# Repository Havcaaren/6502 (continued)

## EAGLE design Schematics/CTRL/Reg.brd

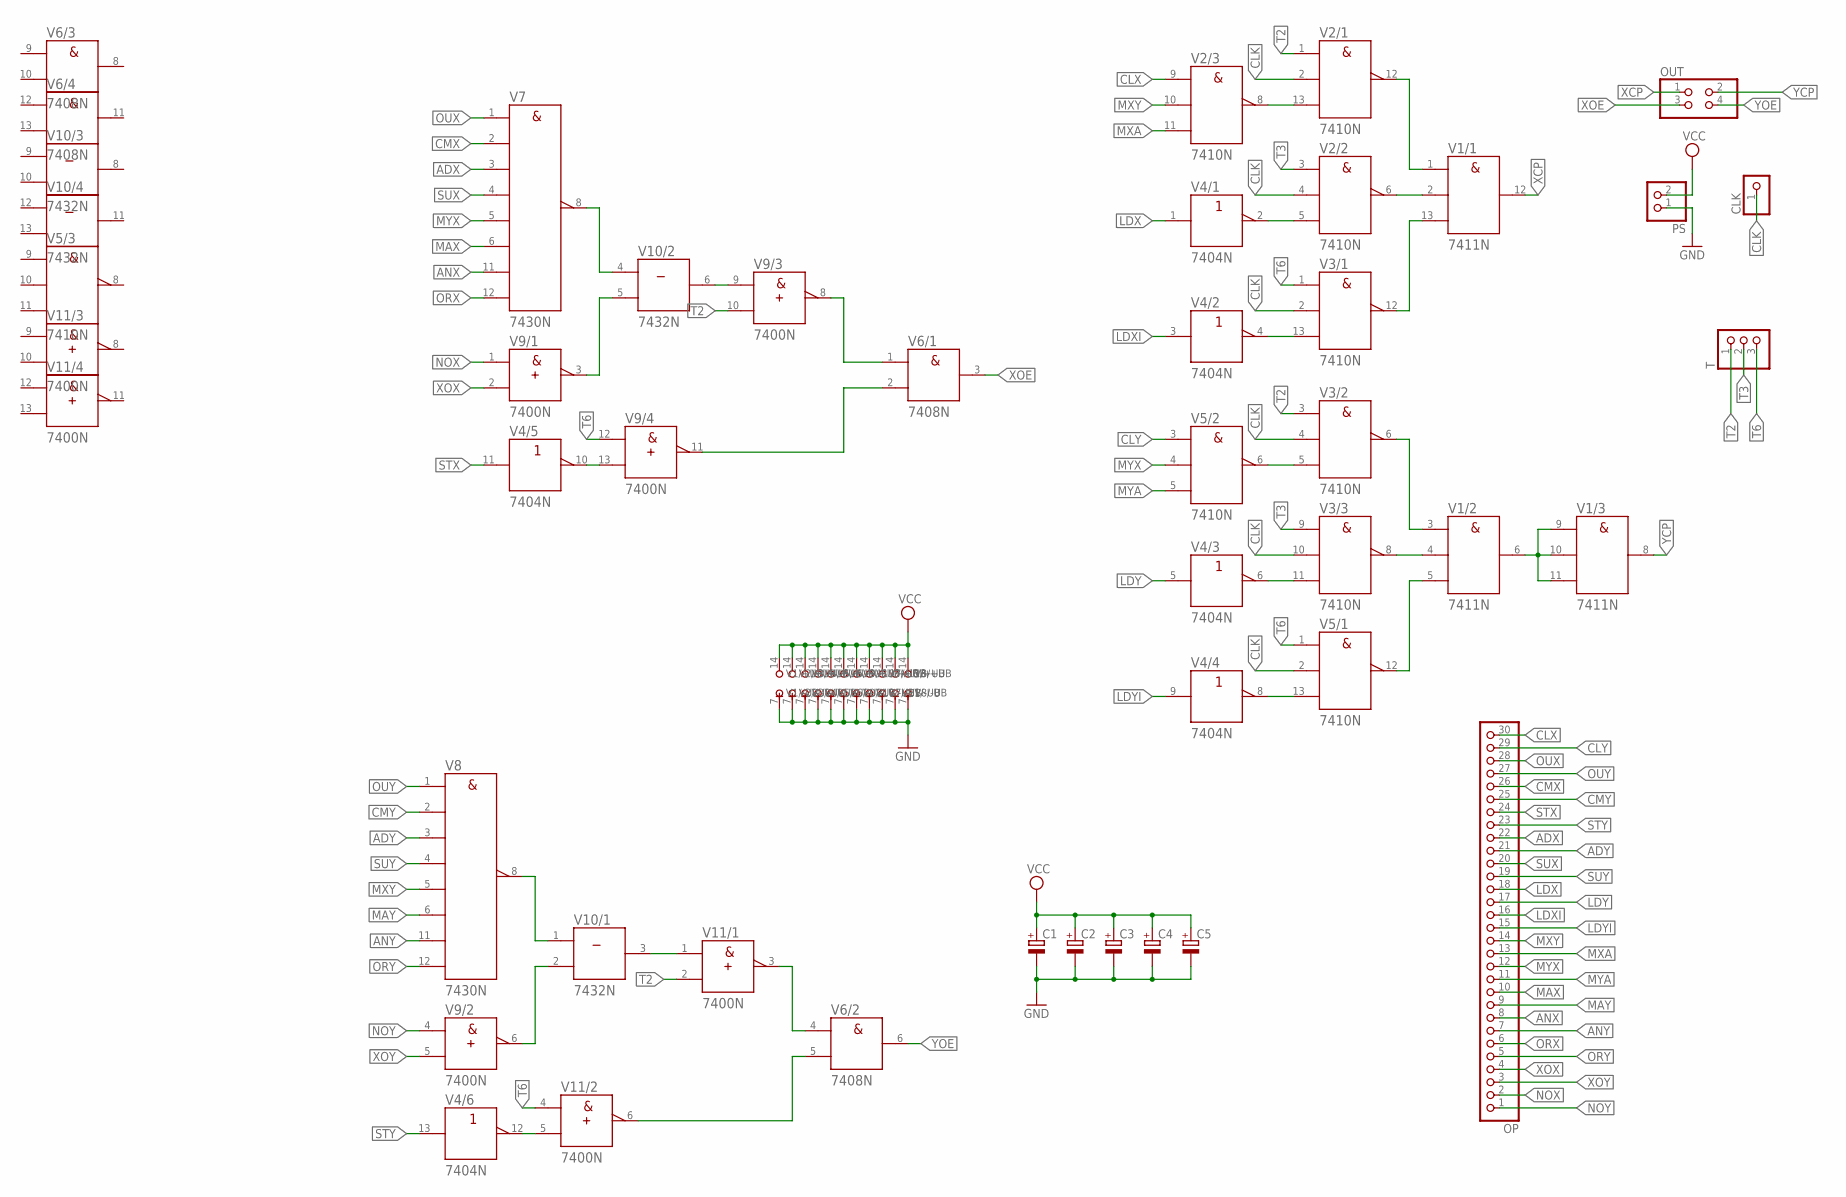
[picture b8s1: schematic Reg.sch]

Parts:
C1, C2, C3, C4, C5: CPOL-EUE2-5; E2-5
CLK: PINHD-1X1; 1X01
OP: PINHD-1X30; 1X30
OUT: PINHD-2X2; 2X02
PS: PINHD-1X2; 1X02
T: PINHD-1X3; 1X03
V1: 7411N; DIL14
V2, V3, V5: 7410N; DIL14
V4: 7404N; DIL14
V6: 7408N; DIL14
V7, V8: 7430N; DIL14
V9, V11: 7400N; DIL14
V10: 7432N; DIL14

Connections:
ADX: OP.22, V7.3 (C)
ADY: OP.21, V8.3 (C)
ANX: OP.8, V7.11 (G)
ANY: OP.7, V8.11 (G)
CLK: CLK.1, V2.2 (B), V2.4 (B), V3.2 (B), V3.4 (B), V3.10 (B), V5.2 (B)
CLX: OP.30, V2.9 (A)
CLY: OP.29, V5.3 (A)
CMX: OP.26, V7.2 (B)
CMY: OP.25, V8.2 (B)
GND: C1.-, C2.-, C3.-, C4.-, C5.-, PS.1, V1.7 (-UB), V2.7 (-UB), V3.7 (-UB), V4.7 (-UB), V5.7 (-UB), V6.7 (-UB), V7.7 (-UB), V8.7 (-UB), V9.7 (-UB), V10.7 (-UB), V11.7 (-UB)
LDX: OP.18, V4.1 (A)
LDXI: OP.16, V4.3 (A)
LDY: OP.17, V4.5 (A)
LDYI: OP.15, V4.9 (A)
MAX: OP.10, V7.6 (F)
MAY: OP.9, V8.6 (F)
MXA: OP.13, V2.11 (C)
MXY: OP.14, V2.10 (B), V8.5 (E)
MYA: OP.11, V5.5 (C)
MYX: OP.12, V5.4 (B), V7.5 (E)
unnamed: V1.3 (A), V3.6 (Y)
unnamed: V1.2 (B), V2.6 (Y)
unnamed: V1.1 (A), V2.12 (Y)
unnamed: V1.13 (C), V3.12 (Y)
unnamed: V1.6 (Y), V1.9 (A), V1.10 (B), V1.11 (C)
unnamed: V1.4 (B), V3.8 (Y)
unnamed: V1.5 (C), V5.12 (Y)
unnamed: V9.9 (A), V10.6 (Y)
unnamed: V4.10 (Y), V9.13 (B)
unnamed: V2.8 (Y), V2.13 (C)
unnamed: V6.1 (A), V9.8 (Y)
unnamed: V6.2 (B), V9.11 (Y)
unnamed: V2.5 (C), V4.2 (Y)
unnamed: V8.8 (Y), V10.1 (A)
unnamed: V9.6 (Y), V10.2 (B)
unnamed: V3.13 (C), V4.4 (Y)
unnamed: V3.5 (C), V5.6 (Y)
unnamed: V10.3 (Y), V11.1 (A)
unnamed: V6.4 (A), V11.3 (Y)
unnamed: V3.11 (C), V4.6 (Y)
unnamed: V4.12 (Y), V11.5 (B)
unnamed: V4.8 (Y), V5.13 (C)
unnamed: V6.5 (B), V11.6 (Y)
unnamed: V7.8 (Y), V10.4 (A)
unnamed: V9.3 (Y), V10.5 (B)
NOX: OP.2, V9.1 (A)
NOY: OP.1, V9.4 (A)
ORX: OP.6, V7.12 (H)
ORY: OP.5, V8.12 (H)
OUX: OP.28, V7.1 (A)
OUY: OP.27, V8.1 (A)
STX: OP.24, V4.11 (A)
STY: OP.23, V4.13 (A)
SUX: OP.20, V7.4 (D)
SUY: OP.19, V8.4 (D)
T2: T.1, V2.1 (A), V3.3 (A), V9.10 (B), V11.2 (B)
T3: T.2, V2.3 (A), V3.9 (A)
T6: T.3, V3.1 (A), V5.1 (A), V9.12 (A), V11.4 (A)
VCC: C1.+, C2.+, C3.+, C4.+, C5.+, PS.2, V1.14 (+UB), V2.14 (+UB), V3.14 (+UB), V4.14 (+UB), V5.14 (+UB), V6.14 (+UB), V7.14 (+UB), V8.14 (+UB), V9.14 (+UB), V10.14 (+UB), V11.14 (+UB)
XCP: OUT.1, V1.12 (Y)
XOE: OUT.3, V6.3 (Y)
XOX: OP.4, V9.2 (B)
XOY: OP.3, V9.5 (B)
YCP: OUT.2, V1.8 (Y)
YOE: OUT.4, V6.6 (Y)

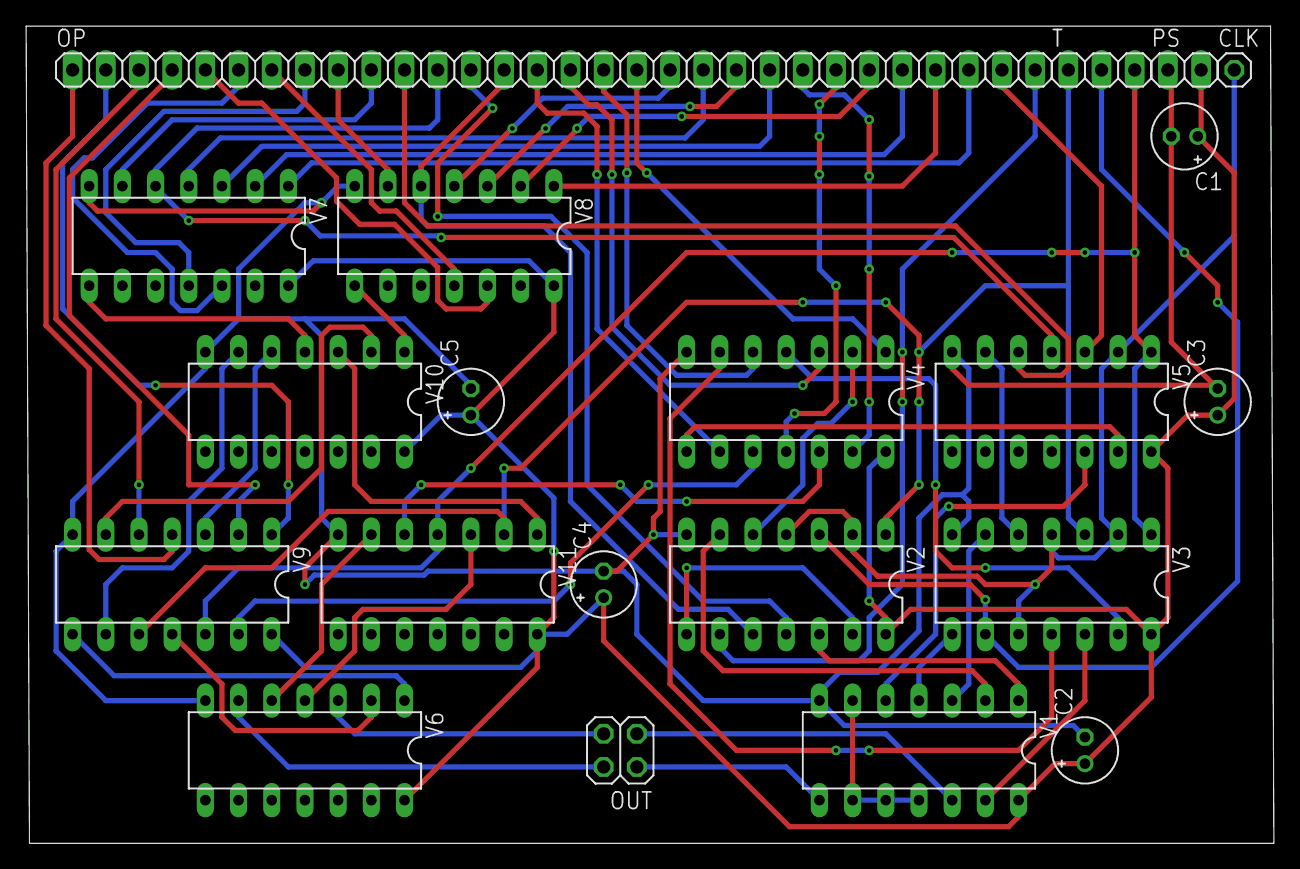
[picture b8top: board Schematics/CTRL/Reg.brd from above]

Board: 2 copper layers, 95.5 x 62.5 mm, 21 parts (0 on the bottom side), 65 nets.

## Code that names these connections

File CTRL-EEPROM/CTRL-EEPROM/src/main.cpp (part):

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};

bool X2[][8] {
/*CLR     PINC PLD PLOE PHOE PCLR POE AOE AOOE*/
/*C0*/    {0,  0,  1,   1,   1,   1,  1,  1},
/*C1*/    {0,  0,  1,   1,   0,   1,  1,  1},
/*C2*/    {0,  0,  1,   1,   0,   1,  1,  1},
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/*C14*/   {0,  0,  1,   1,   0,   0,  1,  1},
/*C15*/   {0,  0,  1,   1,   0,   1,  1,  1},

/*NOP     PINC PLD PLOE PHOE PCLR POE AOE AOOE*/
/*C0*/    {0,  0,  1,   1,   0,   1,  1,  1},
/*C1*/    {0,  0,  1,   1,   0,   1,  1,  1},
/*C2*/    {0,  0,  1,   1,   0,   1,  1,  1},
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/*C14*/   {0,  0,  1,   1,   0,   0,  1,  1},
/*C15*/   {0,  0,  1,   1,   0,   1,  1,  1},

/*OUX     PINC PLD PLOE PHOE PCLR POE AOE AOOE*/
/*C0*/    {0,  0,  1,   1,   0,   1,  1,  1},
/*C1*/    {0,  0,  1,   1,   0,   1,  1,  1},
/*C2*/    {0,  0,  1,   1,   0,   1,  1,  1},
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/*C14*/   {0,  0,  1,   1,   0,   0,  1,  1},
/*C15*/   {0,  0,  1,   1,   0,   1,  1,  1},

/*OUY     PINC PLD PLOE PHOE PCLR POE AOE AOOE*/
/*C0*/    {0,  0,  1,   1,   0,   1,  1,  1},
/*C1*/    {0,  0,  1,   1,   0,   1,  1,  1},
/*C2*/    {0,  0,  1,   1,   0,   1,  1,  1},
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/*C14*/   {0,  0,  1,   1,   0,   0,  1,  1},
/*C15*/   {0,  0,  1,   1,   0,   1,  1,  1},

/*OUA     PINC PLD PLOE PHOE PCLR POE AOE AOOE*/
/*C0*/    {0,  0,  1,   1,   0,   1,  1,  1},
/*C1*/    {0,  0,  1,   1,   0,   1,  0,  1},
/*C2*/    {0,  0,  1,   1,   0,   1,  1,  1},
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/*C14*/   {0,  0,  1,   1,   0,   0,  1,  1},
/*C15*/   {0,  0,  1,   1,   0,   1,  1,  1},

/*CMX     PINC PLD PLOE PHOE PCLR POE AOE AOOE*/
/*C0*/    {0,  0,  1,   1,   0,   1,  1,  1},
/*C1*/    {0,  0,  1,   1,   0,   1,  1,  1},
/*C2*/    {0,  0,  1,   1,   0,   1,  1,  1},
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/*C14*/   {0,  0,  1,   1,   0,   0,  1,  1},
/*C15*/   {0,  0,  1,   1,   0,   1,  1,  1},

/*CMY     PINC PLD PLOE PHOE PCLR POE AOE AOOE*/
/*C0*/    {0,  0,  1,   1,   0,   1,  1,  1},
/*C1*/    {0,  0,  1,   1,   0,   1,  1,  1},
/*C2*/    {0,  0,  1,   1,   0,   1,  1,  1},
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/*C14*/   {0,  0,  1,   1,   0,   0,  1,  1},
/*C15*/   {0,  0,  1,   1,   0,   1,  1,  1},

/*CMV     PINC PLD PLOE PHOE PCLR POE AOE AOOE*/
/*C0*/    {0,  0,  1,   1,   0,   1,  1,  1},
/*C1*/    {1,  0,  1,   1,   0,   1,  1,  1},
/*C2*/    {0,  0,  1,   1,   0,   0,  1,  1},
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/*C14*/   {0,  0,  1,   1,   0,   0,  1,  1},
/*C15*/   {0,  0,  1,   1,   0,   1,  1,  1},

/*JZ      PINC PLD PLOE PHOE PCLR POE AOE AOOE*/
/*C0*/    {0,  0,  1,   1,   0,   1,  1,  1},
/*C1*/    {1,  0,  1,   1,   0,   1,  1,  1},
/*C2*/    {0,  0,  1,   1,   0,   0,  1,  1},
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/*C14*/   {0,  0,  1,   1,   0,   0,  1,  1},
/*C15*/   {0,  0,  1,   1,   0,   1,  1,  1},

/*JN      PINC PLD PLOE PHOE PCLR POE AOE AOOE*/
/*C0*/    {0,  0,  1,   1,   0,   1,  1,  1},
/*C1*/    {1,  0,  1,   1,   0,   1,  1,  1},
/*C2*/    {0,  0,  1,   1,   0,   0,  1,  1},
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/*C14*/   {0,  0,  1,   1,   0,   0,  1,  1},
/*C15*/   {0,  0,  1,   1,   0,   1,  1,  1},

/*JO     PINC PLD PLOE PHOE PCLR POE AOE AOOE*/
/*C0*/    {0,  0,  1,   1,   0,   1,  1,  1},
/*C1*/    {1,  0,  1,   1,   0,   1,  1,  1},
/*C2*/    {0,  0,  1,   1,   0,   0,  1,  1},
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/*C14*/   {0,  0,  1,   1,   0,   0,  1,  1},
/*C15*/   {0,  0,  1,   1,   0,   1,  1,  1},

/*JL     PINC PLD PLOE PHOE PCLR POE AOE AOOE*/
/*C0*/    {0,  0,  1,   1,   0,   1,  1,  1},
/*C1*/    {1,  0,  1,   1,   0,   1,  1,  1},
/*C2*/    {0,  0,  1,   1,   0,   0,  1,  1},
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/*C14*/   {0,  0,  1,   1,   0,   0,  1,  1},
/*C15*/   {0,  0,  1,   1,   0,   1,  1,  1},

/*JG      PINC PLD PLOE PHOE PCLR POE AOE AOOE*/
/*C0*/    {0,  0,  1,   1,   0,   1,  1,  1},
/*C1*/    {1,  0,  1,   1,   0,   1,  1,  1},
/*C2*/    {0,  0,  1,   1,   0,   0,  1,  1},
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/*C14*/   {0,  0,  1,   1,   0,   0,  1,  1},
/*C15*/   {0,  0,  1,   1,   0,   1,  1,  1},

/*JE      PINC PLD PLOE PHOE PCLR POE AOE AOOE*/
/*C0*/    {0,  0,  1,   1,   0,   1,  1,  1},
/*C1*/    {1,  0,  1,   1,   0,   1,  1,  1},
/*C2*/    {0,  0,  1,   1,   0,   0,  1,  1},
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/*C14*/   {0,  0,  1,   1,   0,   0,  1,  1},
/*C15*/   {0,  0,  1,   1,   0,   1,  1,  1},

/*CALL    PINC PLD PLOE PHOE PCLR POE AOE AOOE*/
/*C0*/    {0,  0,  1,   1,   0,   1,  1,  1},
/*C1*/    {1,  0,  1,   1,   0,   1,  1,  1},
/*C2*/    {0,  0,  1,   1,   0,   0,  1,  1},
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/*C14*/   {0,  0,  1,   1,   0,   0,  1,  1},
/*C15*/   {0,  0,  1,   1,   0,   1,  1,  1},

/*RET     PINC PLD PLOE PHOE PCLR POE AOE AOOE*/
/*C0*/    {0,  0,  1,   1,   0,   1,  1,  1},
/*C1*/    {0,  0,  1,   1,   0,   1,  1,  1},
/*C2*/    {0,  0,  1,   1,   0,   1,  1,  1},
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/*C14*/   {0,  0,  1,   1,   0,   0,  1,  1},
/*C15*/   {0,  0,  1,   1,   0,   1,  1,  1},

/*ADX     PINC PLD PLOE PHOE PCLR POE AOE AOOE*/
/*C0*/    {0,  0,  1,   1,   0,   1,  1,  1},
/*C1*/    {0,  0,  1,   1,   0,   1,  1,  1},
/*C2*/    {0,  0,  1,   1,   0,   1,  1,  0},
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/*C14*/   {0,  0,  1,   1,   0,   0,  1,  1},
/*C15*/   {0,  0,  1,   1,   0,   1,  1,  1},

/*ADY     PINC PLD PLOE PHOE PCLR POE AOE AOOE*/
/*C0*/    {0,  0,  1,   1,   0,   1,  1,  1},
/*C1*/    {0,  0,  1,   1,   0,   1,  1,  1},
/*C2*/    {0,  0,  1,   1,   0,   1,  1,  0},
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/*C14*/   {0,  0,  1,   1,   0,   0,  1,  1},
/*C15*/   {0,  0,  1,   1,   0,   1,  1,  1},

/*ADA     PINC PLD PLOE PHOE PCLR POE AOE AOOE*/
/*C0*/    {0,  0,  1,   1,   0,   1,  1,  1},
/*C1*/    {0,  0,  1,   1,   0,   1,  1,  1},
/*C2*/    {0,  0,  1,   1,   0,   1,  0,  0},
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/*C14*/   {0,  0,  1,   1,   0,   0,  1,  1},
/*C15*/   {0,  0,  1,   1,   0,   1,  1,  1},

/*ADV     PINC PLD PLOE PHOE PCLR POE AOE AOOE*/
/*C0*/    {0,  0,  1,   1,   0,   1,  1,  1},
/*C1*/    {1,  0,  1,   1,   0,   1,  1,  1},
/*C2*/    {0,  0,  1,   1,   0,   0,  1,  1},
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/*C14*/   {0,  0,  1,   1,   0,   0,  1,  1},
/*C15*/   {0,  0,  1,   1,   0,   1,  1,  1},

/*ADI     PINC PLD PLOE PHOE PCLR POE AOE AOOE*/
/*C0*/    {0,  0,  1,   1,   0,   1,  1,  1},
/*C1*/    {1,  0,  1,   1,   0,   1,  1,  1},
/*C2*/    {0,  0,  1,   1,   0,   0,  1,  1},
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/*C14*/   {0,  0,  1,   1,   0,   0,  1,  1},
/*C15*/   {0,  0,  1,   1,   0,   1,  1,  1},

/*SUX     PINC PLD PLOE PHOE PCLR POE AOE AOOE*/
/*C0*/    {0,  0,  1,   1,   0,   1,  1,  1},
/*C1*/    {0,  0,  1,   1,   0,   1,  1,  1},
/*C2*/    {0,  0,  1,   1,   0,   1,  1,  0},
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/*C14*/   {0,  0,  1,   1,   0,   0,  1,  1},
/*C15*/   {0,  0,  1,   1,   0,   1,  1,  1},

/*SUY     PINC PLD PLOE PHOE PCLR POE AOE AOOE*/
/*C0*/    {0,  0,  1,   1,   0,   1,  1,  1},
/*C1*/    {0,  0,  1,   1,   0,   1,  1,  1},
/*C2*/    {0,  0,  1,   1,   0,   1,  1,  0},
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/*C14*/   {0,  0,  1,   1,   0,   0,  1,  1},
/*C15*/   {0,  0,  1,   1,   0,   1,  1,  1},

/*SUA     PINC PLD PLOE PHOE PCLR POE AOE AOOE*/
/*C0*/    {0,  0,  1,   1,   0,   1,  1,  1},
/*C1*/    {0,  0,  1,   1,   0,   1,  1,  1},
/*C2*/    {0,  0,  1,   1,   0,   1,  0,  0},
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/*C14*/   {0,  0,  1,   1,   0,   0,  1,  1},
/*C15*/   {0,  0,  1,   1,   0,   1,  1,  1},

/*SUV     PINC PLD PLOE PHOE PCLR POE AOE AOOE*/
/*C0*/    {0,  0,  1,   1,   0,   1,  1,  1},
/*C1*/    {1,  0,  1,   1,   0,   1,  1,  1},
/*C2*/    {0,  0,  1,   1,   0,   0,  1,  1},
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/*C14*/   {0,  0,  1,   1,   0,   0,  1,  1},
/*C15*/   {0,  0,  1,   1,   0,   1,  1,  1},

/*SUI     PINC PLD PLOE PHOE PCLR POE AOE AOOE*/
/*C0*/    {0,  0,  1,   1,   0,   1,  1,  1},
/*C1*/    {1,  0,  1,   1,   0,   1,  1,  1},
/*C2*/    {0,  0,  1,   1,   0,   0,  1,  1},
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/*C14*/   {0,  0,  1,   1,   0,   0,  1,  1},
/*C15*/   {0,  0,  1,   1,   0,   1,  1,  1},

/*STX     PINC PLD PLOE PHOE PCLR POE AOE AOOE*/
/*C0*/    {0,  0,  1,   1,   0,   1,  1,  1},
/*C1*/    {1,  0,  1,   1,   0,   1,  1,  1},
/*C2*/    {0,  0,  1,   1,   0,   0,  1,  1},
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/*C14*/   {0,  0,  1,   1,   0,   0,  1,  1},
/*C15*/   {0,  0,  1,   1,   0,   1,  1,  1},

/*STY     PINC PLD PLOE PHOE PCLR POE AOE AOOE*/
/*C0*/    {0,  0,  1,   1,   0,   1,  1,  1},
/*C1*/    {1,  0,  1,   1,   0,   1,  1,  1},
/*C2*/    {0,  0,  1,   1,   0,   0,  1,  1},
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/*C14*/   {0,  0,  1,   1,   0,   0,  1,  1},
/*C15*/   {0,  0,  1,   1,   0,   1,  1,  1},

/*STA     PINC PLD PLOE PHOE PCLR POE AOE AOOE*/
/*C0*/    {0,  0,  1,   1,   0,   1,  1,  1},
/*C1*/    {1,  0,  1,   1,   0,   1,  1,  1},
/*C2*/    {0,  0,  1,   1,   0,   0,  1,  1},
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/*C14*/   {0,  0,  1,   1,   0,   0,  1,  1},
/*C15*/   {0,  0,  1,   1,   0,   1,  1,  1},

/*LDX     PINC PLD PLOE PHOE PCLR POE AOE AOOE*/
/*C0*/    {0,  0,  1,   1,   0,   1,  1,  1},
/*C1*/    {1,  0,  1,   1,   0,   1,  1,  1},
/*C2*/    {0,  0,  1,   1,   0,   0,  1,  1},
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/*C14*/   {0,  0,  1,   1,   0,   0,  1,  1},
/*C15*/   {0,  0,  1,   1,   0,   1,  1,  1},

/*LDY     PINC PLD PLOE PHOE PCLR POE AOE AOOE*/
/*C0*/    {0,  0,  1,   1,   0,   1,  1,  1},
/*C1*/    {1,  0,  1,   1,   0,   1,  1,  1},
/*C2*/    {0,  0,  1,   1,   0,   0,  1,  1},
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/*C14*/   {0,  0,  1,   1,   0,   0,  1,  1},
/*C15*/   {0,  0,  1,   1,   0,   1,  1,  1},

/*LDA     PINC PLD PLOE PHOE PCLR POE AOE AOOE*/
/*C0*/    {0,  0,  1,   1,   0,   1,  1,  1},
/*C1*/    {1,  0,  1,   1,   0,   1,  1,  1},
/*C2*/    {0,  0,  1,   1,   0,   0,  1,  1},
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/*C14*/   {0,  0,  1,   1,   0,   0,  1,  1},
/*C15*/   {0,  0,  1,   1,   0,   1,  1,  1},

/*LDXI    PINC PLD PLOE PHOE PCLR POE AOE AOOE*/
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
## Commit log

2021-06-10 Readme
2021-06-11 started working on Program Counter.
2021-06-11 readme update
2021-06-12 Added first version of Program Counter.
2021-06-12 Fixed README and removed old version of PC (.brd and .sch)
2021-06-12 Added foto of program counter
2021-06-14 Added section for ALU.
2021-06-14 Added datasheet for original MOS6502.
2021-06-14 added git ignore
2021-06-14 added *.pro
2021-06-14 renamed files
2021-06-14 Added link to datasheet
2021-06-15 Changed direction of this project.
    Building replica od Mos 6502, is hard and I have only one year to complete it.
2021-06-15 Added DCE-malvino. SAP-2 base of my computer
2021-06-26 Redo PC.
2021-07-01 PC need to be reworked
2021-07-02 Started working on c++ simulation of 8bit cpu.
2021-07-02 final version of PC.
    Final version of program counter before building one.
2021-07-04 Added clock sch.
2021-07-04 .pro for PC
2021-07-08 Reworked program simulation. Controller not working.
2021-07-08 Controller simulation.
2021-07-08 Added list of intructions, need to add op codes.
2021-07-09 Added op codes, started working on simulation of controller
2021-07-09 Added more op codes.
2021-07-13 README.md update
2021-07-15 Started working on simulation in logisim-evolution.
2021-07-15 Sim update.
2021-07-30 Schematic for registers.
2021-07-30 Small updates.
2021-07-30 Schematic for bus to X, Y register.
2021-08-01 Added first version of Program Counter. Probably will by broken down to smaller modules.
2021-08-01 Started reworking C++ simulation of CPU.
2021-08-02 Schematic for PC, PC-register and PC-bus.
2021-08-02 Move register-bus to Register folder
2021-08-02 Added datasheets for 286 and 86.
2021-08-04 Added full add/sub and register for ACC and B
2021-08-05 ALU need to be redone.
2021-08-09 Added fotos of sch and brd of PC and register.
2021-08-09 Added todo file.
2021-08-09 README.md update.
2021-08-09 Mirror brd.
2021-08-09 Added fotos and CAM for pc-bus
2021-08-09 Added sch, brd, CAM and fotos for ALU-ACC.
2021-08-10 Update to register schematic. Wrong connection on DIR pin of LS245.
2021-08-10 Modified register-bus to fit new register brd.
2021-08-10 Added sch and brd for ALU-B, sch, brd and gerber for pc register.
2021-08-10 PC doesnt need EN pin.
2021-08-13 Main brd
2021-08-14 TMP (B) register doesnt need buffers.
2021-08-14 Added 74LS85 (CMP) datasheet.
2021-08-14 Added datasheet for AT28C64 (EEPROM) - RAM
2021-08-14 Register brd now have X and Y reg.
2021-08-14 Removed Main and Register sch, brd.
2021-08-14 Removed some parts of README.md
2021-08-15 Added 395 and 299 datasheet
2021-08-15 Added High overview of CPU.
2021-08-15 Removed 299.
2021-08-17 Added datasheet for 02, 04, 08, 30, 32.
2021-08-17 Schematic for ALU and Registers on one brd.
2021-08-18 Removed CUBE-1.pdf
2021-08-18 Added first schematic and board for ALU and Registers
2021-08-18 Removed simulation of CPU.
2021-08-18 Removed fotos folder fotos now in schematics folder
2021-08-20 Added few caps to power line.
2021-08-23 Removed ALU and register brd cannot order 6layer brd
2021-08-23 Added sch, brd, gerber for register.
2021-08-23 Added LED to register.
2021-08-23 Updated Diagram
2021-08-25 Added sch, brd and gerber file for register, register bus, pc and ROM.
2021-08-25 L6 was on bottom not top.
2021-08-25 Eagle didnt saw VCC as connected.
2021-08-25 Added pdf (fotos) of schematic and board of register.
2021-08-25 Added pdf (fotos) of schematic and board of register-bus.
2021-08-25 Readme update.
2021-08-26 Added pdf for PC-ROM and pc-bus.
2021-08-26 .gitignore update.
2021-08-26 Added resistors to rom address.
2021-09-01 Register bus final " version\.
2021-09-01 Added RAM module.
2021-09-01 Started working on compiler for CPU + example of CASM(Castom Assembly).
2021-09-01 . gitignore update
2021-09-01 IO file, LDR
2021-09-10 Added fotos for PC and Registers .
2021-09-10 Gitignore update
2021-09-10 Added functio to parse OP.
2021-09-11 inner labels and HLT op
2021-09-11 small updates in parser
2021-09-11 Main label working no jmp
2021-09-12 PC can now output to bus. Merged PC, PC-Bus and ROM.
2021-09-12 Merged Register and Register-bus.
2021-09-12 Edited frame name.
2021-09-12 RAM merged with register.
2021-09-13 Added sch and brd for ALU (400x110)mm.
2021-09-13 Updated README.
2021-09-13 Removed sim folder
2021-09-13 Fixed link for sch.
2021-09-13 Started working on Output sch. Maybe later will add serial and paralel output .
2021-09-19 git ignore update
2021-09-19 parser 90% working.
2021-09-20 Added LDR.
2021-10-02 Added register, ALU (missing shift L, R), PC and Rom.
2021-10-02 Removed few file
2021-10-02 Moved schematic.sch to root dir.
2021-10-08 Renamed the compiler
2021-10-08 Opcodes and RJP docx
2021-10-09 Added Schematic and Board for registers X, Y.
2021-10-09 Changed OP codes.
2021-10-10 Renamed parser to Rosetta Stone
2021-10-10 Working parser.
2021-10-10 Edited few op.
2021-10-10 Update to OP and RPJ
2021-10-10 Added sch and brd for RAM, PC
2021-10-10 ignore update
2021-10-10 Fully working Compiler
2021-10-10 Added Compiler section in README
2021-10-10 Removed Z from register
2021-10-11 fixed Logic OPs
2021-10-11 Added control for multiple labels.
2021-10-12 Commiting ALU so I dont lose it.
2021-10-13 RPJ update
2021-10-13 Added register.
2021-10-15 Register, PC, RAM will be solid board not modules, brd is pretty simple.
2021-10-16 Register and RAM modules.
2021-10-16 Added PC and ROM
2021-10-16 Added TODOs.
2021-10-17 Added ACC and Logic (AND, OR, XOR).
2021-10-17 Added NOT.
2021-10-17 Correct page number for NOT
2021-10-17 Added Summer
2021-10-19 Added backbone for ALU.
2021-10-19 RJP update.
2021-10-19 Renamed .casm to .asm
2021-10-19 Started working on -O3.
2021-10-19 Renamed ANA to AND
2021-10-20 RS update.
2021-10-23 Added folder for Eeprom writter.
2021-10-23 Basic data printing.
2021-10-23 Parser now have logger
2021-10-23 Removed LD-V instruction
2021-10-23 DS for 138
2021-10-24 Added Decoder sch, brd, zip
2021-10-24 Added DB for 109
2021-10-26 Added few ctrl steps for few instustions
2021-10-27 CTRL simulation in logic sim.
2021-10-27 Added model of CPU
2021-10-28 OP pins for few OP.
2021-10-29 OP pins for every OP
2021-10-29 Tring sch,brd
2021-10-29 Fixed major mistakes.
2021-10-30 CTRL sim update
2021-10-30 IR reg now have cp pin
2021-11-09 RPJ update.
2021-11-28 RS update
2021-12-03 added bus term and output reg + small update to RS
2021-12-04 Better table for instructio/Tring
2021-12-04 Reduce Tring width
2021-12-05 Added clock
2021-12-05 Moved clock
2021-12-05 Update to OP and added B-out.
2021-12-05 Added RJP
2021-12-06 Changed order of LEDs and widht is now 11bits (0-10).
2021-12-07 Created table for OPs
2021-12-07 Small changes to ALU ops
2021-12-07 First and hopefully last version of Control sch.
2021-12-08 Schematics for V1
2021-12-11 Added xlsx for IC and other componets.
2021-12-11 Added pdf with all schematic missing CTRL-main and BUS, BUS-out
2021-12-11 Added $ to .org addr
2021-12-11 Working Lexer
2021-12-12 Reduce asm code.
2021-12-12 test tokenized and findLabel
2021-12-12 TODOS
2021-12-13 OR 20 -> ORV 20
2021-12-15 Added function for variables. Not implemented.
2021-12-19 Reworking lexer
2021-12-19 Video of PC working
2021-12-21 Fixed 2 problems, that I found after ordering boards
2021-12-21 Made some changes' compilation not working.
2021-12-21 Started to completely reworking RS.
2021-12-26 Fixed DIR pin on HOE and LOE. Found when I was testing real brd.
2021-12-26 Removed all gerber files half of them have problem sch and brd will be fixed gerber not.
2021-12-29 OP.txt is the correct hex numbers for OPs
2021-12-29 Fixed ACC mid pins now in correct order, Adder still have ACC and BUS switched.
2021-12-29 Removed Compiler from readme
2021-12-30 Fixed Adder inputs and added LEDs for ZF, OF and NF.
2021-12-30 Created func that returns map with every OP + size.
2021-12-30 TODO finish insert and writing to out.bin.
2022-01-01 Label rename.
2022-01-01 added spaces
2022-01-01 Working address insert
2022-01-01 Correct OPs.
2022-01-01 Fully working compiler.
2022-01-01 Now can be compiled with c++3
2022-01-01 Added compiler to README.md
2022-01-01 Added fotos of boards
2022-01-02 Changed typ of output. Not parsing negative numbers.
2022-01-03 Decimal still not working
2022-01-03 Only hex mod.
2022-01-03 127 number out of range max FF. +<00-7F> , -<80-FF>
2022-01-03 Started working on logic control.
2022-01-03 Now correctly output numbers and addresses.
2022-01-04 Better CTRL list for OPs
2022-01-06 CTRL update
2022-01-06 CTRL v1.1 final version I hope so.
2022-01-08 Added pull down resisotors to NAND gates. Maybe 'single' will be button.
2022-01-08 'Final' version of Compiler.
2022-01-08 RM CMakeLists
2022-01-09 RAM, REG and PC ctrl completed. working on ALU
2022-01-09 ALU CTRL.
2022-01-09 Final version of CTRL-bus. last brd is bus.
2022-01-09 IC list for ctrl.
2022-01-12 Added bus, fixed C1 on ALU-CTRL, CLK.zip, added 7410 to ctrl so bus out will work*.
2022-01-12 Create LICENSE
2022-01-12 added last missing IC
2022-01-15 removed not needed files renamed Photos
2022-01-16 Updated version of pdf schematics
2022-01-19 Removed -L
2022-02-11 Fixed problem with 0xXX
    RET wasnt negated, 0xFF and 0xFE started to over heat when T2 was High.
2022-02-20 new version of control brd using EEPROMs.
    I have only 5 EEPROM (AT28C64), and stores such as TME or SOS elctronic, Avelmak do not have them. :(
2022-02-20 .gitignore
2022-02-20 pio init
2022-02-20 All states for eeproms
2022-03-05 fixet version of new ctrl
2022-03-31 RS for new controller
2022-04-02 jump instuction
2022-04-14 rm ram module
2022-04-14 control for bad labels
    OP code still can by a problem when used as label
2022-04-16 Arduino eeprom writter
2022-04-16 Added fotos and RPJ doc
2022-04-19 OP code numbers fixed
2022-04-19 Changed op code of HLT to 128
2022-04-19 fixed programer
2022-04-19 added fib in asm.
    compiler not working correctly
2022-04-19 readme clr
2022-04-19 Create fib_no_loop
2022-04-22 fixed .asm
2022-04-22 fixed labels.
2022-04-27 fixed opcode of jmp op
2022-04-27 fixed PLD
2022-05-01 Last (probably) changes to CTRL brd.
2022-05-01 Changed jmp ops, becouse of CTRL brd changes
2022-05-01 Last version of fib program
2022-05-01 Blink program
2022-05-16 last version
